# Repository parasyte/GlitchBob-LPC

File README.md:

# GlitchBob LPC

Voltage glitching automation tool to break protection on NXP LPC microcontrollers.

The glitch circuit can be controlled by a Raspberry Pi Pico or other low-cost development board.

## TODO

These are issues identified in the prototype:

- Add bypass caps to all ICs.
- Add pull-up resistor to `74LVC1G3157` switch input.
- Add pull-down resistors to `74LVC2G66` switch inputs.
- Move target closer to I/O header to reduce the trace length for the oscillator I/O.
    - Shorter traces have lower impedance and will be capable of faster clock frequency (up to target max, e.g. 12 MHz).
- The potentiometer polarity is swapped.
    - 0v should be fully counterclockwise, and +VCC should be fully clockwise.
- The potentiometer is upside down.
    - Rotate the footprint 180 degrees.
- No good place to put the rubber feet.
    - Move through-hole components or find smaller feet.
- Still has some wasted surface area with traces spread out.
    - Change 8-pin header pinout to optimize routing.
    - Move traces closer together to prevent ground plane islands.
- `R3` is a bit too close to the serial port.
    - Move `R3` so it is more easily reachable for assembly.

And this is a wish-list for improvements:

- Replace 8-pin header with Raspberry Pi Pico header footprint.
- Add a 7-segment display for glitch-voltage display and other info.
    - 7-Segment driver can be inexpensively built with:
        - [`74LVC244`](https://www.mouser.com/ProductDetail/Texas-Instruments/SN74LVC244APWR?qs=DcvZ7Fltd5xns%252BvAsbES0A%3D%3D) or [`74HC244`](https://www.mouser.com/ProductDetail/Nexperia/74HC244PW118?qs=sGAEpiMZZMutXGli8Ay4kE3wRMDwmh%2F%252B519e17hTwKc%3D) - Octal buffer/line-driver.
        - [`74LV4052`](https://www.mouser.com/ProductDetail/Nexperia/74LV4052PW118?qs=me8TqzrmIYXk9tz3ZPOozg%3D%3D) or [`74HC4052`](https://www.mouser.com/ProductDetail/Nexperia/74HC4052D653?qs=P62ublwmbi9dOtwH%252Bhrppg%3D%3D) - 4-channel analog multiplexer/demultiplexer.
        - [`LTC-5723HR`](https://www.mouser.com/ProductDetail/Lite-On/LTC-5723HR?qs=WxFF5lh7QM2ytJdX1EhJKQ%3D%3D) - 4-digit 7-segment display with common cathode.
- Optional ADC for potentiometer measurement.
    - Using Raspberry Pi Pico's ADC for target voltage up to 3.3v <code>V<sub>RL</sub></code>.
    - A standalone ADC will allow a second power rail for the target voltage, e.g. up to 5v <code>V<sub>RL</sub></code> with [`TLA2021`](https://www.mouser.com/ProductDetail/Texas-Instruments/TLA2021IRUGT?qs=sGAEpiMZZMtgJDuTUz7Xu52YdifX%2FxP9lhA%252BBqDZ7rN1fYamX3qf2A%3D%3D) - 12-bit ADC, I<sup>2</sup>C.
- Replacing the analog potentiometer with a digital encoder + DAC can allow finer adjustment of the glitch-voltage.
    - No ADC is required with this setup.
    - Fully software-controlled; E.g. allows ignoring rotations while automated search is running.
    - Example components:
        - [`PEC12R-4215F-S0024`](https://www.mouser.com/ProductDetail/Bourns/PEC12R-4215F-S0024?qs=pxDZlBjcsCiq%252B%252BLwoVCNNg%3D%3D) - Contact incremental encoder with switch, 2-bit quadrature code, 24 pulses per rotation.
        - [`1106`](https://www.mouser.com/ProductDetail/Davies-Molding/1106?qs=byeeYqUIh0Mr0LdKOAGzbA%3D%3D) Knob for encoder, black and blue.
        - [`MCP47CVB21`](https://www.mouser.com/ProductDetail/Microchip-Technology-Atmel/MCP47CVB21-E-MG?qs=sGAEpiMZZMtgJDuTUz7Xu2gekaVOgz%252BBwkrv3p3aJpfVVhvcYLmSXw%3D%3D) - 12-bit DAC, I<sup>2</sup>C.
    - Encoder switch can be used to change the sensitivity.
        - Debounce in software.
        - Operation is software controlled. E.g. push to switch to next in a list of two or more settings, push-and-hold to start automated search, etc.
        - Sensitivities are software controlled. E.g. 0.25v per pulse, 0.01v per pulse, etc. As low as <code>V<sub>RL</sub>/4096</code> (limited by DAC resolution).

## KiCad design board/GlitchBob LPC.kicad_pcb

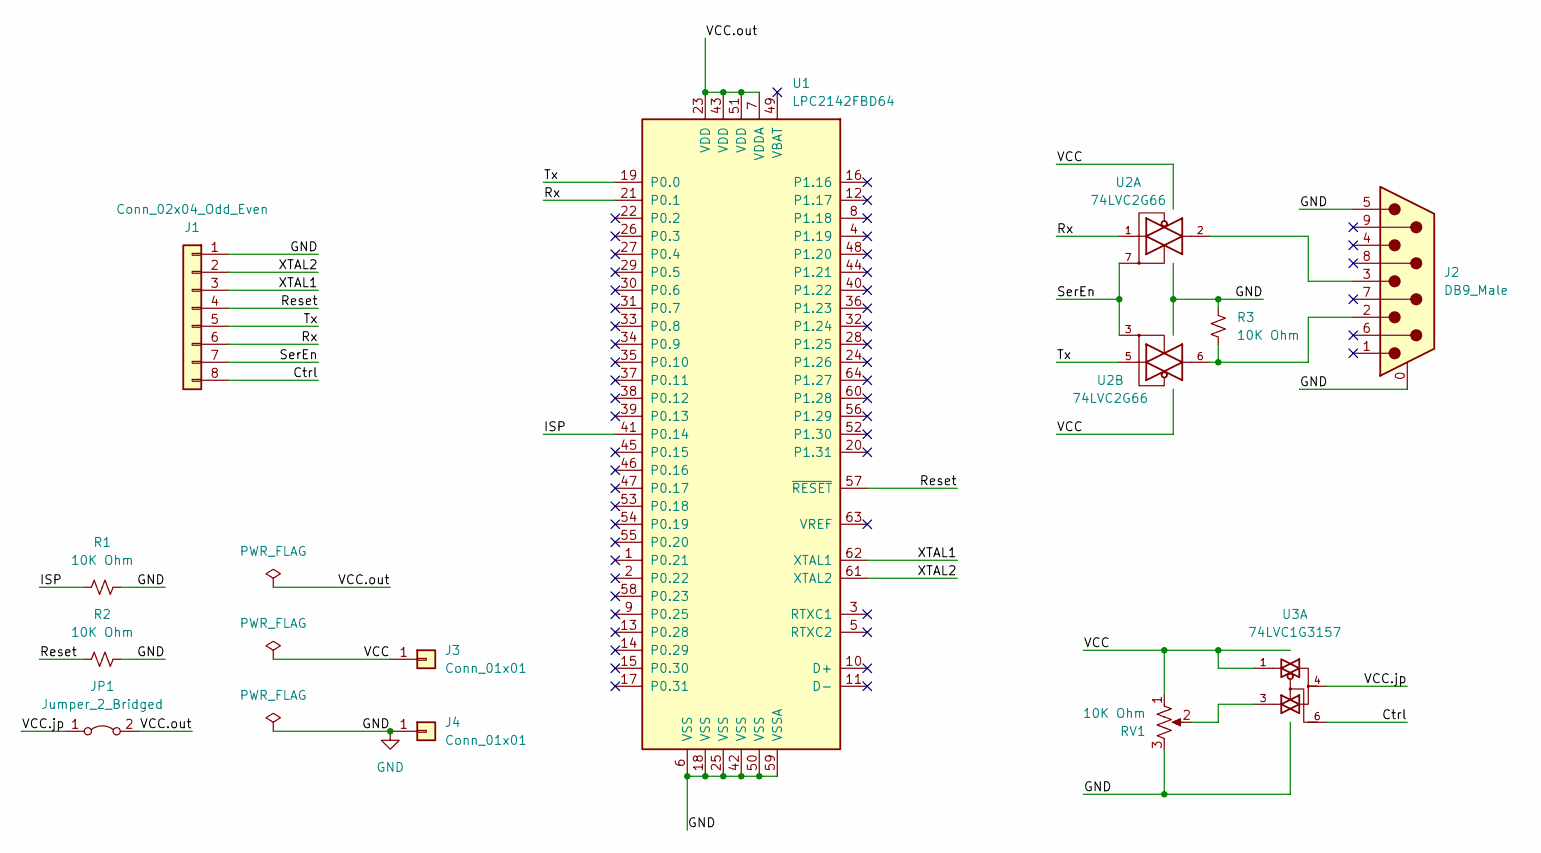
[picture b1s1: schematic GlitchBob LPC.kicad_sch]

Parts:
J1: Conn_02x04_Odd_Even; PinHeader_1x08_P2.54mm_Vertical
J2: DB9_Male; DSUB-9_Male_Horizontal_P2.77x2.84mm_EdgePinOffset7.70mm_Hou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
J3, J4: Conn_01x01; PinHeader_1x01_P2.54mm_Vertical
JP1: Jumper_2_Bridged; PinHeader_1x02_P2.54mm_Vertical
R1, R2, R3: 10K Ohm; R_0805_2012Metric
RV1: 10K Ohm; Potentiometer_Alps_RK09K_Single_Vertical
U1: LPC2142FBD64; LQFP-64_10x10mm_P0.5mm
U2: 74LVC2G66; TSSOP-8_3x3mm_P0.65mm
U3: 74LVC1G3157; TSOP-6_1.65x3.05mm_P0.95mm

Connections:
/Ctrl: J1.8, U3.6
/ISP: R1.1, U1.41 (P0.14)
/Reset: J1.4, R2.1, U1.57 (~RESET)
/Rx: J1.6, U1.21 (P0.1), U2.1
/SerEn: J1.7, U2.3, U2.7
/Tx: J1.5, U1.19 (P0.0), U2.5
/VCC.jp: JP1.1 (A), U3.4
/VCC.out: JP1.2 (B), U1.7 (VDDA), U1.23 (VDD), U1.43 (VDD), U1.51 (VDD)
/XTAL1: J1.3, U1.62 (XTAL1)
/XTAL2: J1.2, U1.61 (XTAL2)
GND: J1.1, J2.0 (PAD), J2.5, J4.1, R1.2, R2.2, R3.2, RV1.3, RV1.MP, U1.6 (VSS), U1.18 (VSS), U1.25 (VSS), U1.42 (VSS), U1.50 (VSS), U1.59 (VSSA), U2.4 (GND), U3.2 (GND)
unnamed: J2.2, R3.1, U2.6
unnamed: J2.3, U2.2
unnamed: RV1.2, U3.3
VCC: J3.1, RV1.1, U2.8 (VCC), U3.1, U3.5 (VCC)

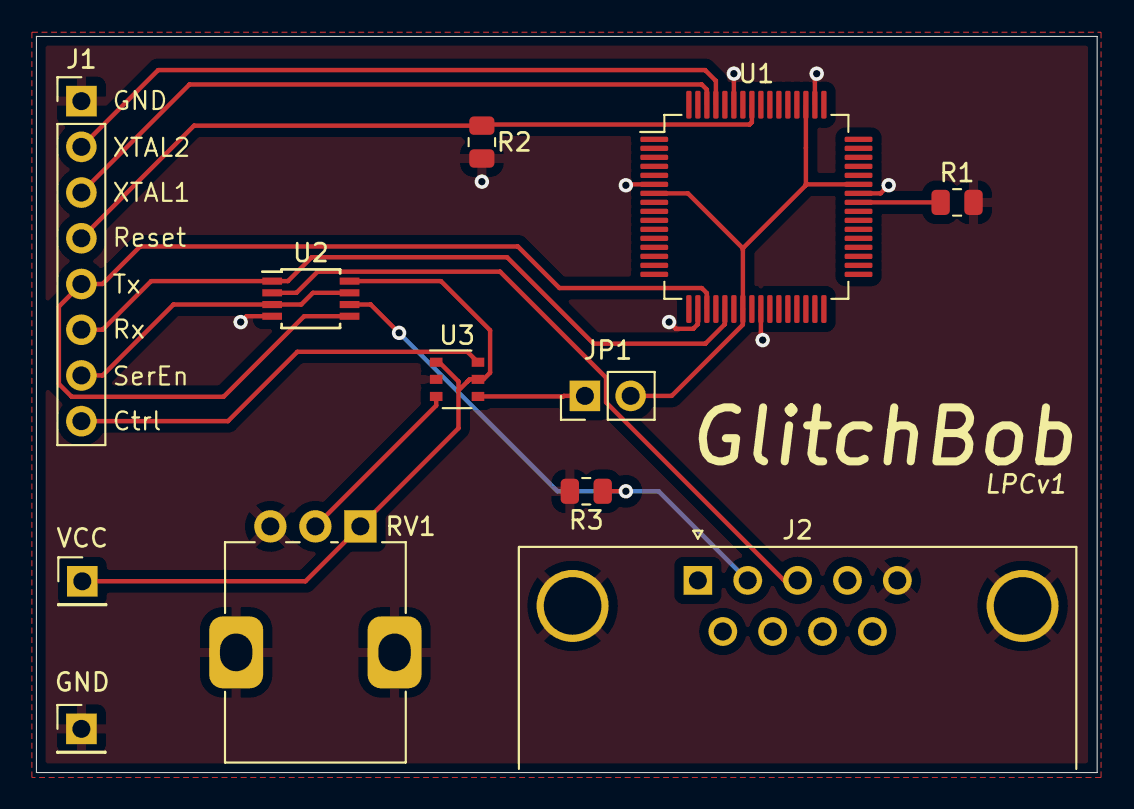
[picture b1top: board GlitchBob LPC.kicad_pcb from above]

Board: 2 copper layers, 58.9 x 40.9 mm, 12 parts (0 on the bottom side), 15 nets.

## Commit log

2022-09-24 Add digital encoder and DAC option to wish-list.
    - Researched component options and provided recommendations based on
    availability, price, and feature set.
2022-10-06 Add photo of assembled device
